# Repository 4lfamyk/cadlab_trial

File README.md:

View this project on [CADLAB.io](https://cadlab.io/node/875). 

# cadlab_trial

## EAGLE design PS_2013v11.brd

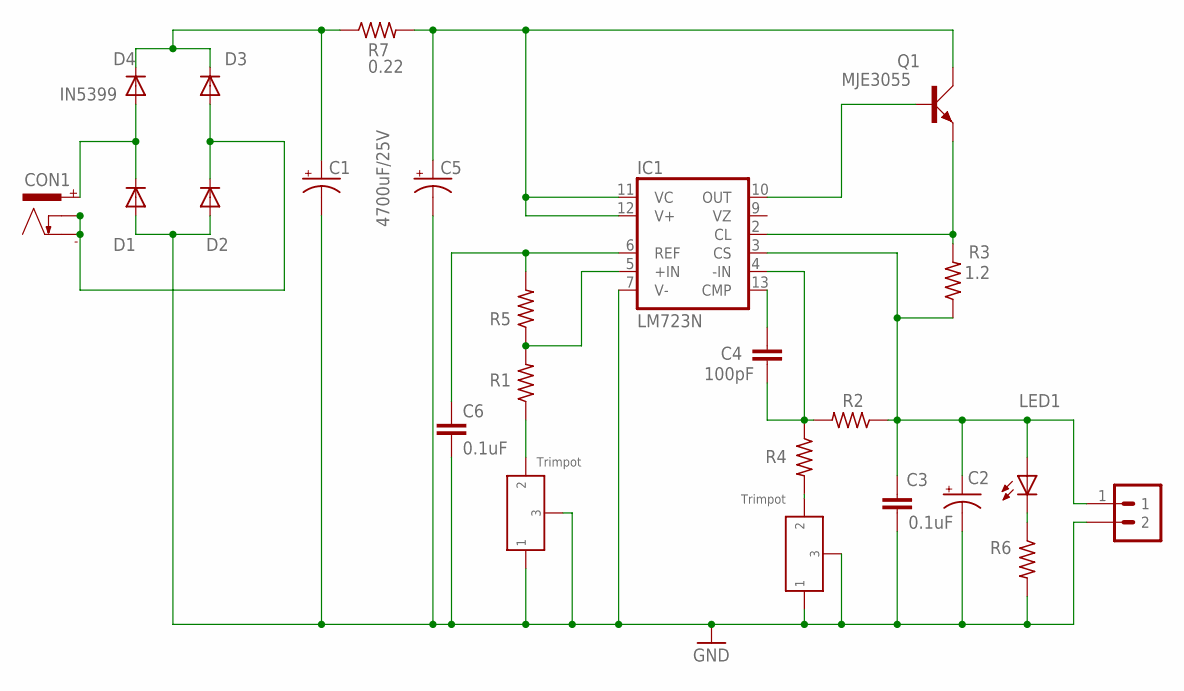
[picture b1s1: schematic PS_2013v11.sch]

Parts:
C1: CPOL-USE7.5-18; E7,5-18
C2: CPOL-USE2,5-6E; E2,5-6E
C3, C6: 0.1uF; C050-024X044
C4: 100pF; C050-024X044
C5: 4700uF/25V; E7,5-18
CON1: POWER_CON; NEB21R
D1, D2, D3, D4: IN5399; DO15-12
IC1: LM723N; DIL14
LED1: LED3MM
Q1: MJE3055; TO220AV
R1: 560k; 0204/5
R2, R4: 300k; 0204/5
R3: 1.2; 0617/22
R5: 220k; 0204/5
R6: 330; 0204/5
R7: 0.22; 0617/22
U$1, U$3: PRESET; PRESET_PACK
U$4: 1X2_LR

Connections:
unnamed: IC1.5 (+IN), R1.2, R5.1
unnamed: C6.1, IC1.6 (REF), R5.2
unnamed: IC1.10 (OUT), Q1.B
unnamed: C4.1, IC1.13 (CMP)
unnamed: IC1.2 (CL), Q1.E, R3.2
unnamed: C1.+, D3.C, D4.C, R7.1
unnamed: R1.1, U$1.P$2 (2)
unnamed: C4.2, IC1.4 (-IN), R2.2, R4.1
unnamed: C5.+, IC1.11 (VC), IC1.12 (V+), Q1.C, R7.2
unnamed: R4.2, U$3.P$2 (2)
unnamed: LED1.K (C), R6.1
unnamed: CON1.+, D1.C, D4.A
unnamed: C2.+, C3.1, IC1.3 (CS), LED1.A, R2.1, R3.1, U$4.1
unnamed: CON1.-, CON1.C, D2.C, D3.A
PRESET2: C1.-, C2.-, C3.2, C5.-, C6.2, D1.A, D2.A, IC1.7 (V-), R6.2, U$1.P$1 (1), U$1.P$3 (3), U$3.P$1 (1), U$3.P$3 (3), U$4.2

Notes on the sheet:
Trimpot

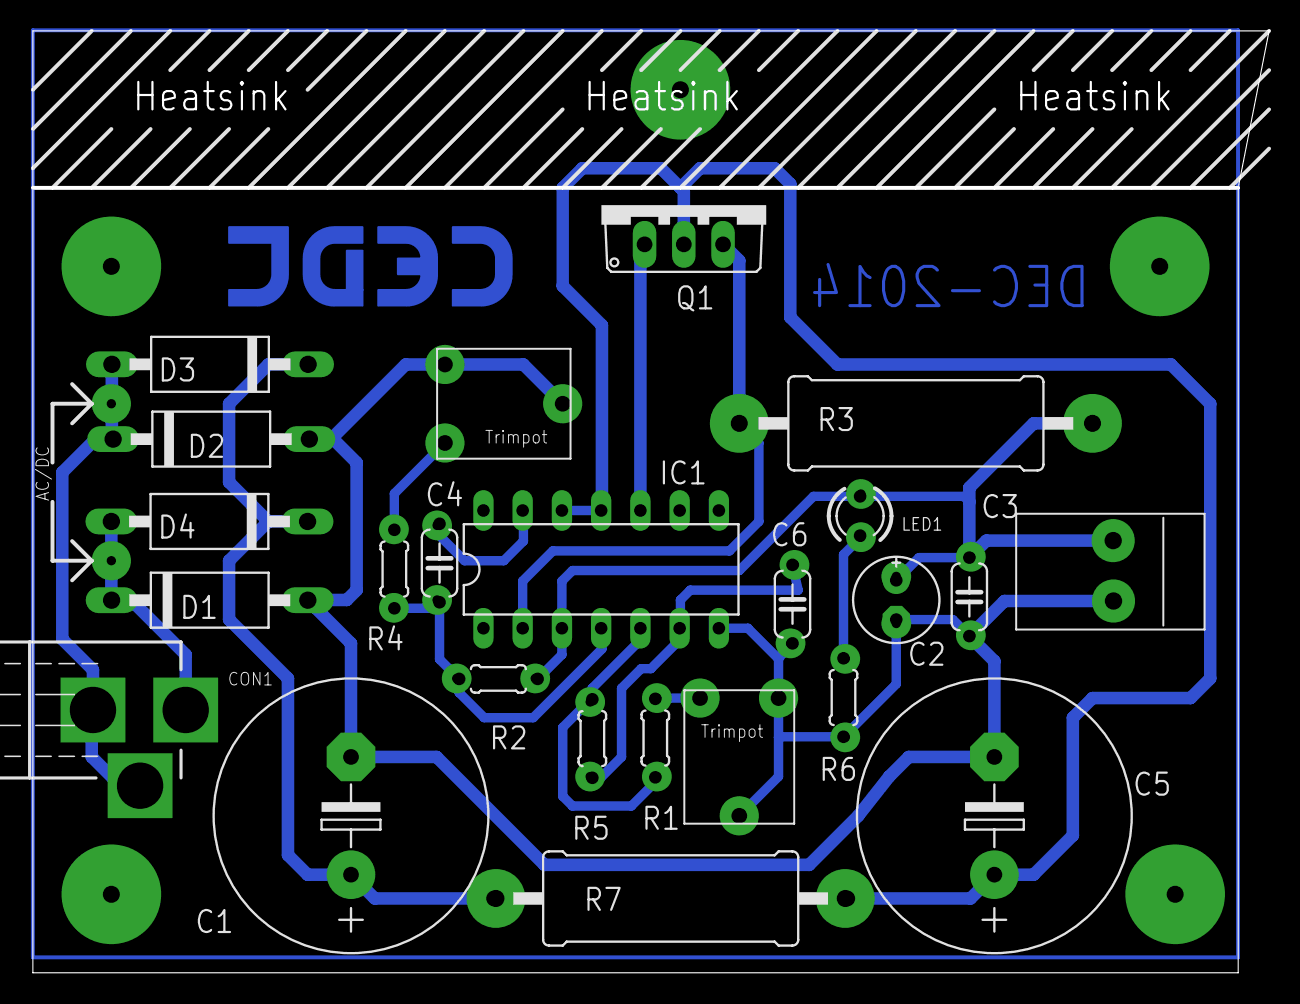
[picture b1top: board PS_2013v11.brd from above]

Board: 2 copper layers, 79.9 x 60.7 mm, 25 parts (0 on the bottom side), 15 nets.

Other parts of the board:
U$2: LOGO-CEDT-BOT-18MM

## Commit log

2018-04-13 Backlink to CADLAB.io has been added.
